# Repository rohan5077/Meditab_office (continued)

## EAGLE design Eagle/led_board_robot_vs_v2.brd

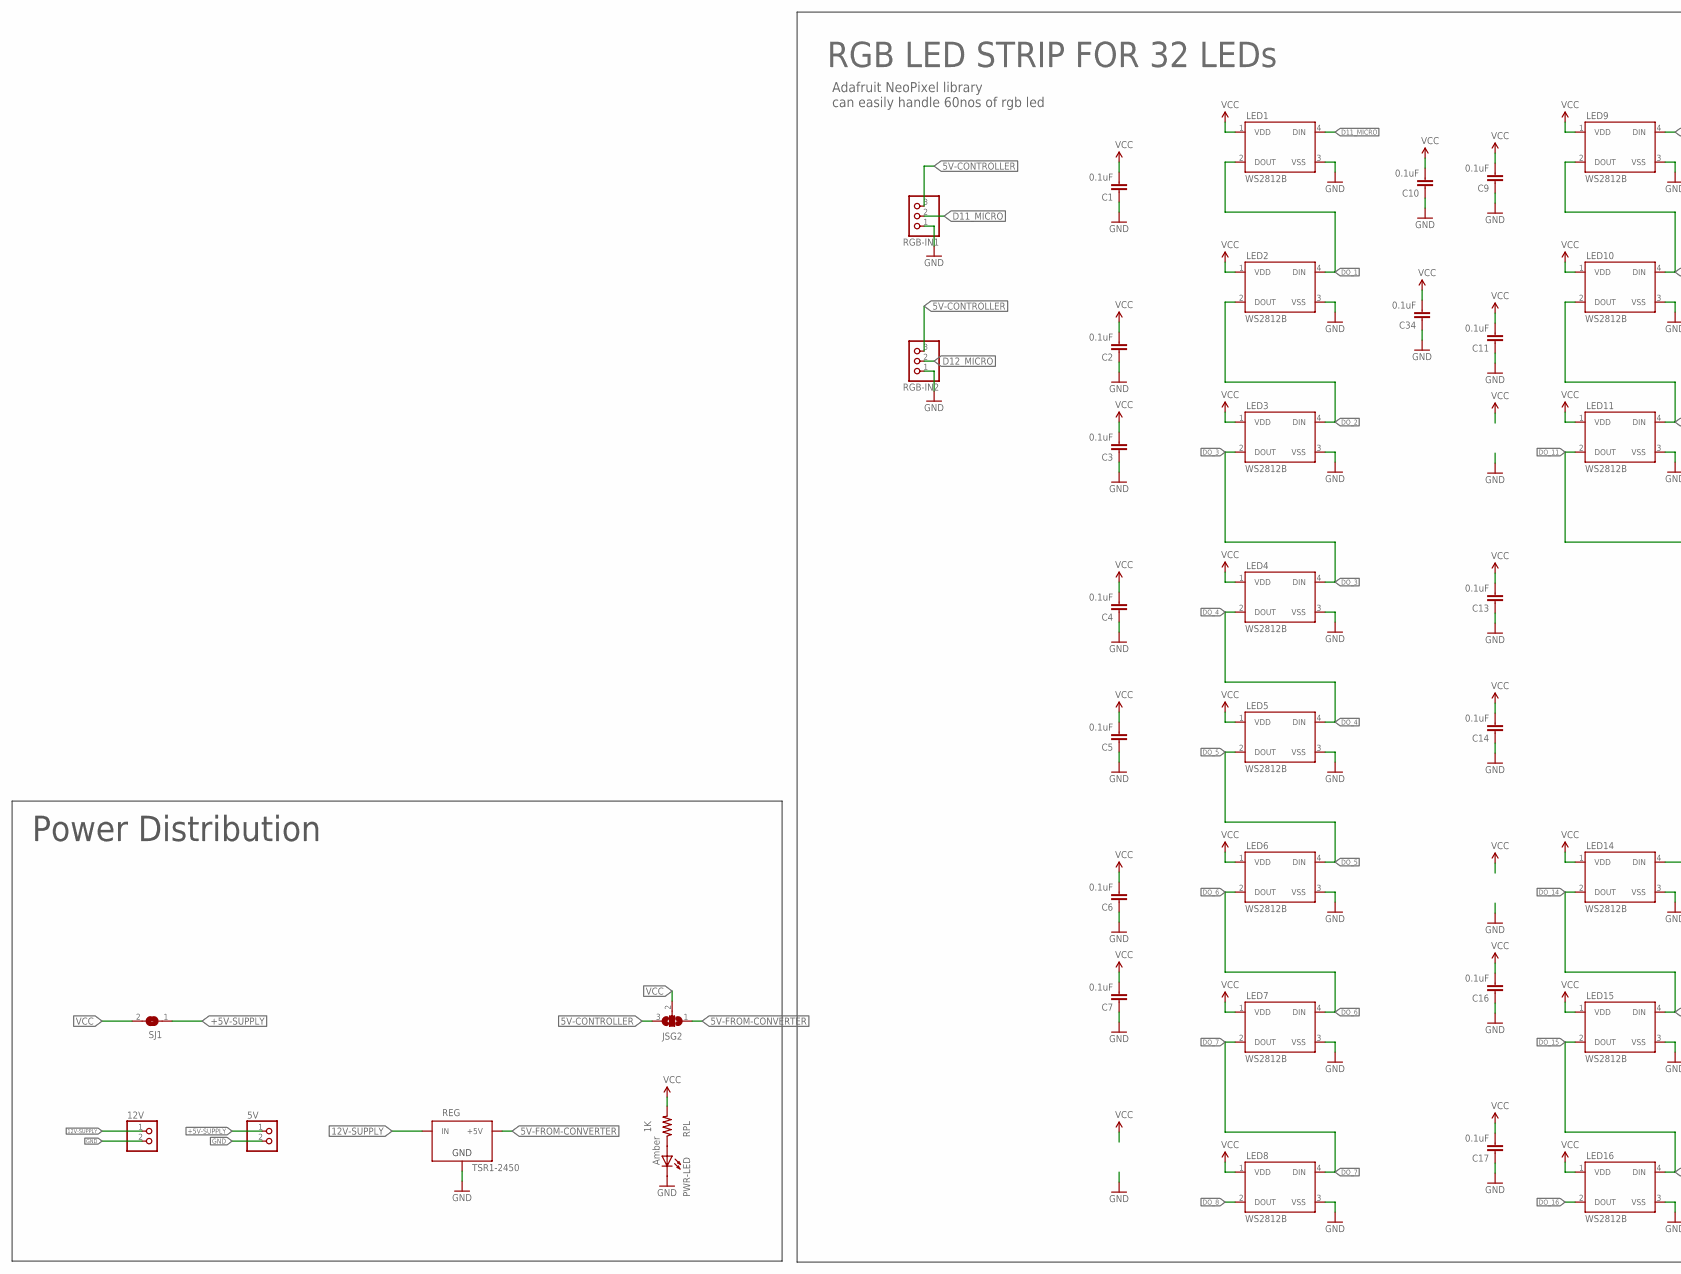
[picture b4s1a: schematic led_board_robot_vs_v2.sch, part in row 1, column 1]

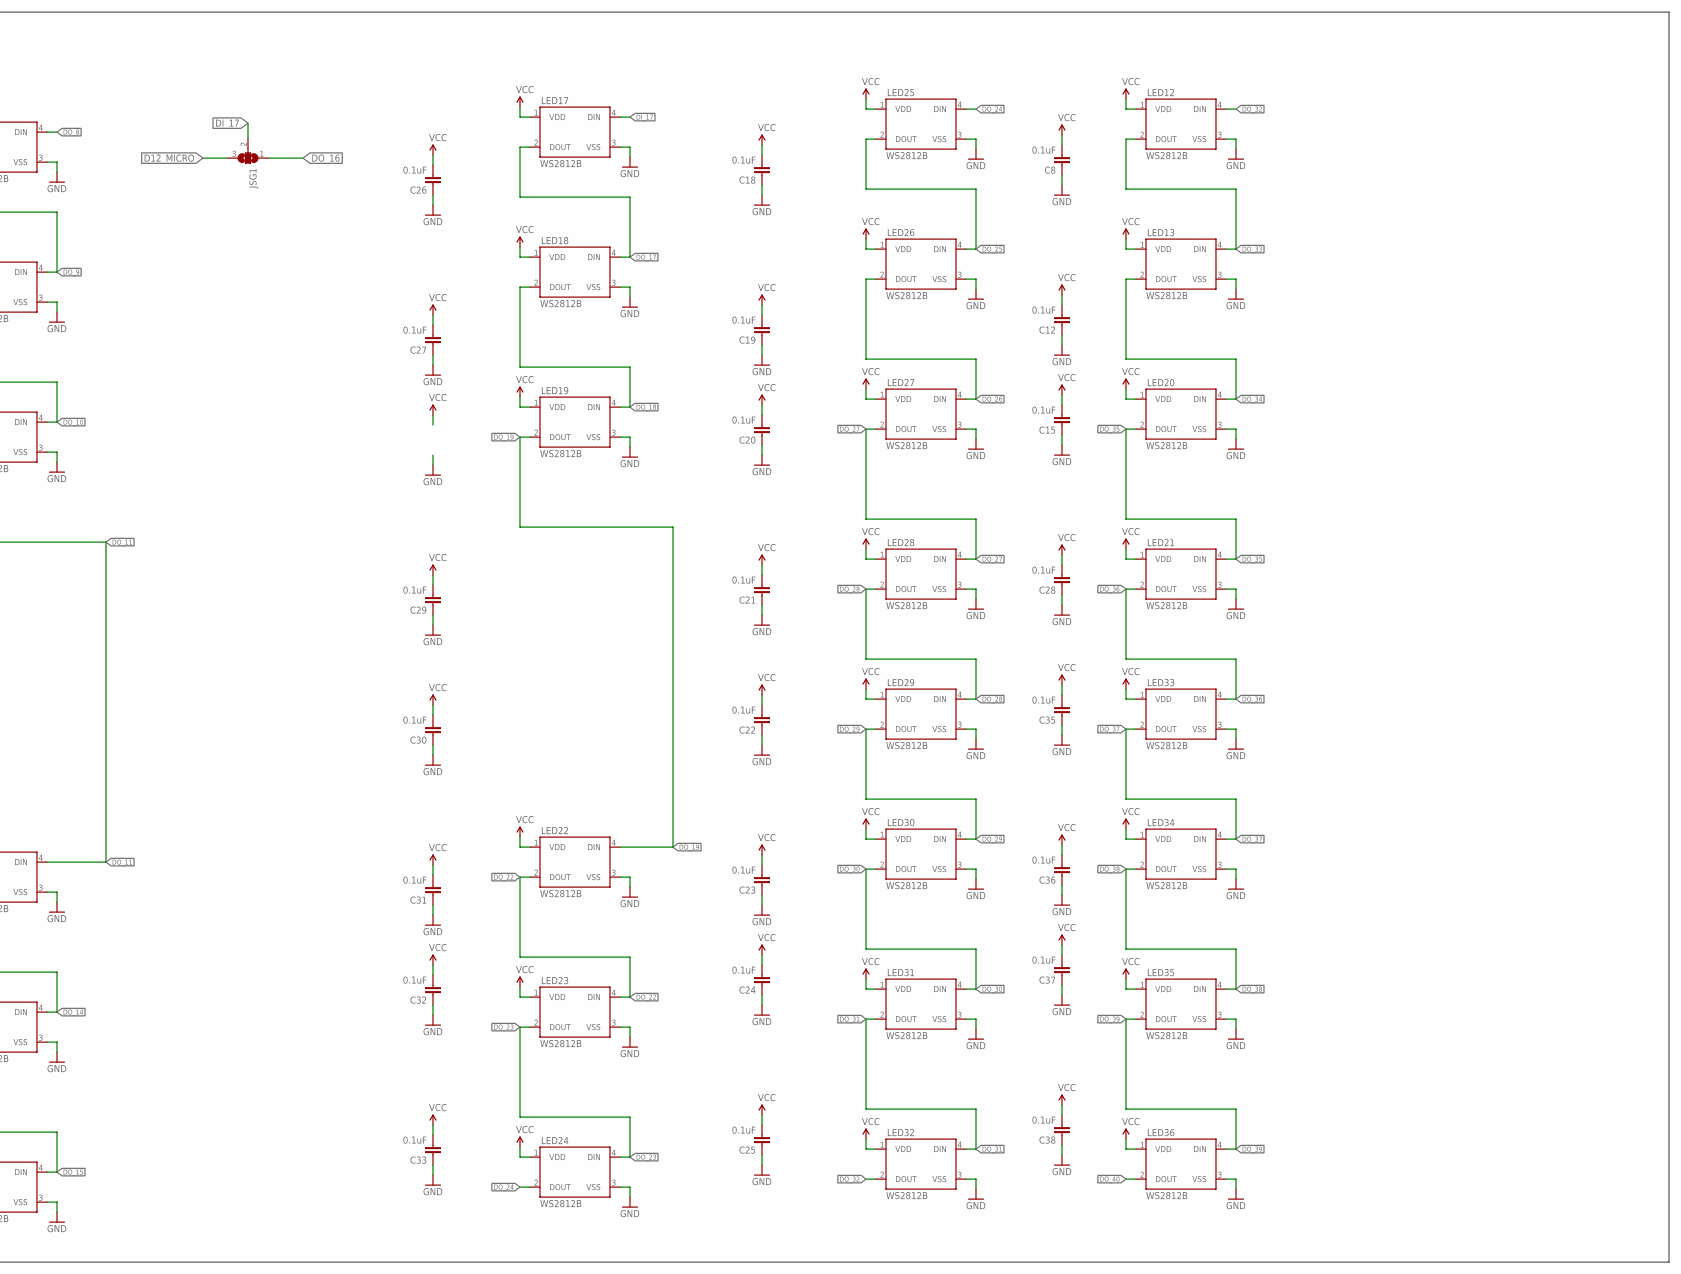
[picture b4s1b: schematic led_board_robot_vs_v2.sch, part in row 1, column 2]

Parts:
5V, 12V: PINHD-1X2; 1X02
C1, C2, C3, C4, C5, C6, C7, C8, C9, C10, C11, C12, C13, C14, C15, C16, C17, C18, C19, C20, C21, C22, C23, C24, C25, C26, C27, C28, C29, C30, C31, C32, C33, C34, C35, C36, C37, C38: 0.1uF; 0603-CAP
JSG1, JSG2: SJ2WW; SJ_2W
LED1, LED2, LED3, LED4, LED5, LED6, LED7, LED8, LED9, LED10, LED11, LED12, LED13, LED14, LED15, LED16, LED17, LED18, LED19, LED20, LED21, LED22, LED23, LED24, LED25, LED26, LED27, LED28, LED29, LED30, LED31, LED32, LED33, LED34, LED35, LED36: WS2812B
PWR-LED: Amber; LED-0603
REG: TSR1-2450; TSR-1
RGB-IN1, RGB-IN2: PINHD-1X3; 1X03
RPL: 1K; 0603-RES
SJ1: SJW

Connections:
5V-CONTROLLER: JSG2.3, RGB-IN1.3, RGB-IN2.3
5V-FROM-CONVERTER: JSG2.1, REG.3 (+5V)
12V-SUPPLY: 12V.1, REG.1 (IN)
+5V-SUPPLY: 5V.1, SJ1.1
D11_MICRO: LED1.4 (DIN), RGB-IN1.2
D12_MICRO: JSG1.3, RGB-IN2.2
DI_17: JSG1.2, LED17.4 (DIN)
DO_1: LED1.2 (DOUT), LED2.4 (DIN)
DO_2: LED2.2 (DOUT), LED3.4 (DIN)
DO_3: LED3.2 (DOUT), LED4.4 (DIN)
DO_4: LED4.2 (DOUT), LED5.4 (DIN)
DO_5: LED5.2 (DOUT), LED6.4 (DIN)
DO_6: LED6.2 (DOUT), LED7.4 (DIN)
DO_7: LED7.2 (DOUT), LED8.4 (DIN)
DO_8: LED8.2 (DOUT), LED9.4 (DIN)
DO_9: LED9.2 (DOUT), LED10.4 (DIN)
DO_10: LED10.2 (DOUT), LED11.4 (DIN)
DO_11: LED11.2 (DOUT), LED14.4 (DIN)
DO_14: LED14.2 (DOUT), LED15.4 (DIN)
DO_15: LED15.2 (DOUT), LED16.4 (DIN)
DO_16: JSG1.1, LED16.2 (DOUT)
DO_17: LED17.2 (DOUT), LED18.4 (DIN)
DO_18: LED18.2 (DOUT), LED19.4 (DIN)
DO_19: LED19.2 (DOUT), LED22.4 (DIN)
DO_22: LED22.2 (DOUT), LED23.4 (DIN)
DO_23: LED23.2 (DOUT), LED24.4 (DIN)
DO_24: LED24.2 (DOUT), LED25.4 (DIN)
DO_25: LED25.2 (DOUT), LED26.4 (DIN)
DO_26: LED26.2 (DOUT), LED27.4 (DIN)
DO_27: LED27.2 (DOUT), LED28.4 (DIN)
DO_28: LED28.2 (DOUT), LED29.4 (DIN)
DO_29: LED29.2 (DOUT), LED30.4 (DIN)
DO_30: LED30.2 (DOUT), LED31.4 (DIN)
DO_31: LED31.2 (DOUT), LED32.4 (DIN)
DO_32: LED12.4 (DIN), LED32.2 (DOUT)
DO_33: LED12.2 (DOUT), LED13.4 (DIN)
DO_34: LED13.2 (DOUT), LED20.4 (DIN)
DO_35: LED20.2 (DOUT), LED21.4 (DIN)
DO_36: LED21.2 (DOUT), LED33.4 (DIN)
DO_37: LED33.2 (DOUT), LED34.4 (DIN)
DO_38: LED34.2 (DOUT), LED35.4 (DIN)
DO_39: LED35.2 (DOUT), LED36.4 (DIN)
DO_40: LED36.2 (DOUT)
GND: 5V.2, 12V.2, C1.1, C2.1, C3.1, C4.1, C5.1, C6.1, C7.1, C8.1, C9.1, C10.1, C11.1, C12.1, C13.1, C14.1, C15.1, C16.1, C17.1, C18.1, C19.1, C20.1, C21.1, C22.1, C23.1, C24.1, C25.1, C26.1, C27.1, C28.1, C29.1, C30.1, C31.1, C32.1, C33.1, C34.1, C35.1, C36.1, C37.1, C38.1, LED1.3 (VSS), LED2.3 (VSS), LED3.3 (VSS), LED4.3 (VSS), LED5.3 (VSS), LED6.3 (VSS), LED7.3 (VSS), LED8.3 (VSS), LED9.3 (VSS), LED10.3 (VSS), LED11.3 (VSS), LED12.3 (VSS), LED13.3 (VSS), LED14.3 (VSS), LED15.3 (VSS), LED16.3 (VSS), LED17.3 (VSS), LED18.3 (VSS), LED19.3 (VSS), LED20.3 (VSS), LED21.3 (VSS), LED22.3 (VSS), LED23.3 (VSS), LED24.3 (VSS), LED25.3 (VSS), LED26.3 (VSS), LED27.3 (VSS), LED28.3 (VSS), LED29.3 (VSS), LED30.3 (VSS), LED31.3 (VSS), LED32.3 (VSS), LED33.3 (VSS), LED34.3 (VSS), LED35.3 (VSS), LED36.3 (VSS), PWR-LED.C, REG.2 (GND), RGB-IN1.1, RGB-IN2.1
unnamed: PWR-LED.A, RPL.1
VCC: C1.2, C2.2, C3.2, C4.2, C5.2, C6.2, C7.2, C8.2, C9.2, C10.2, C11.2, C12.2, C13.2, C14.2, C15.2, C16.2, C17.2, C18.2, C19.2, C20.2, C21.2, C22.2, C23.2, C24.2, C25.2, C26.2, C27.2, C28.2, C29.2, C30.2, C31.2, C32.2, C33.2, C34.2, C35.2, C36.2, C37.2, C38.2, JSG2.2, LED1.1 (VDD), LED2.1 (VDD), LED3.1 (VDD), LED4.1 (VDD), LED5.1 (VDD), LED6.1 (VDD), LED7.1 (VDD), LED8.1 (VDD), LED9.1 (VDD), LED10.1 (VDD), LED11.1 (VDD), LED12.1 (VDD), LED13.1 (VDD), LED14.1 (VDD), LED15.1 (VDD), LED16.1 (VDD), LED17.1 (VDD), LED18.1 (VDD), LED19.1 (VDD), LED20.1 (VDD), LED21.1 (VDD), LED22.1 (VDD), LED23.1 (VDD), LED24.1 (VDD), LED25.1 (VDD), LED26.1 (VDD), LED27.1 (VDD), LED28.1 (VDD), LED29.1 (VDD), LED30.1 (VDD), LED31.1 (VDD), LED32.1 (VDD), LED33.1 (VDD), LED34.1 (VDD), LED35.1 (VDD), LED36.1 (VDD), RPL.2, SJ1.2

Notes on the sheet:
Adafruit NeoPixel library can easily handle 60nos of rgb led
RGB LED STRIP FOR 32 LEDs
Power Distribution

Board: 2 copper layers, 84 parts (2 on the bottom side), 45 nets, no tracks yet.

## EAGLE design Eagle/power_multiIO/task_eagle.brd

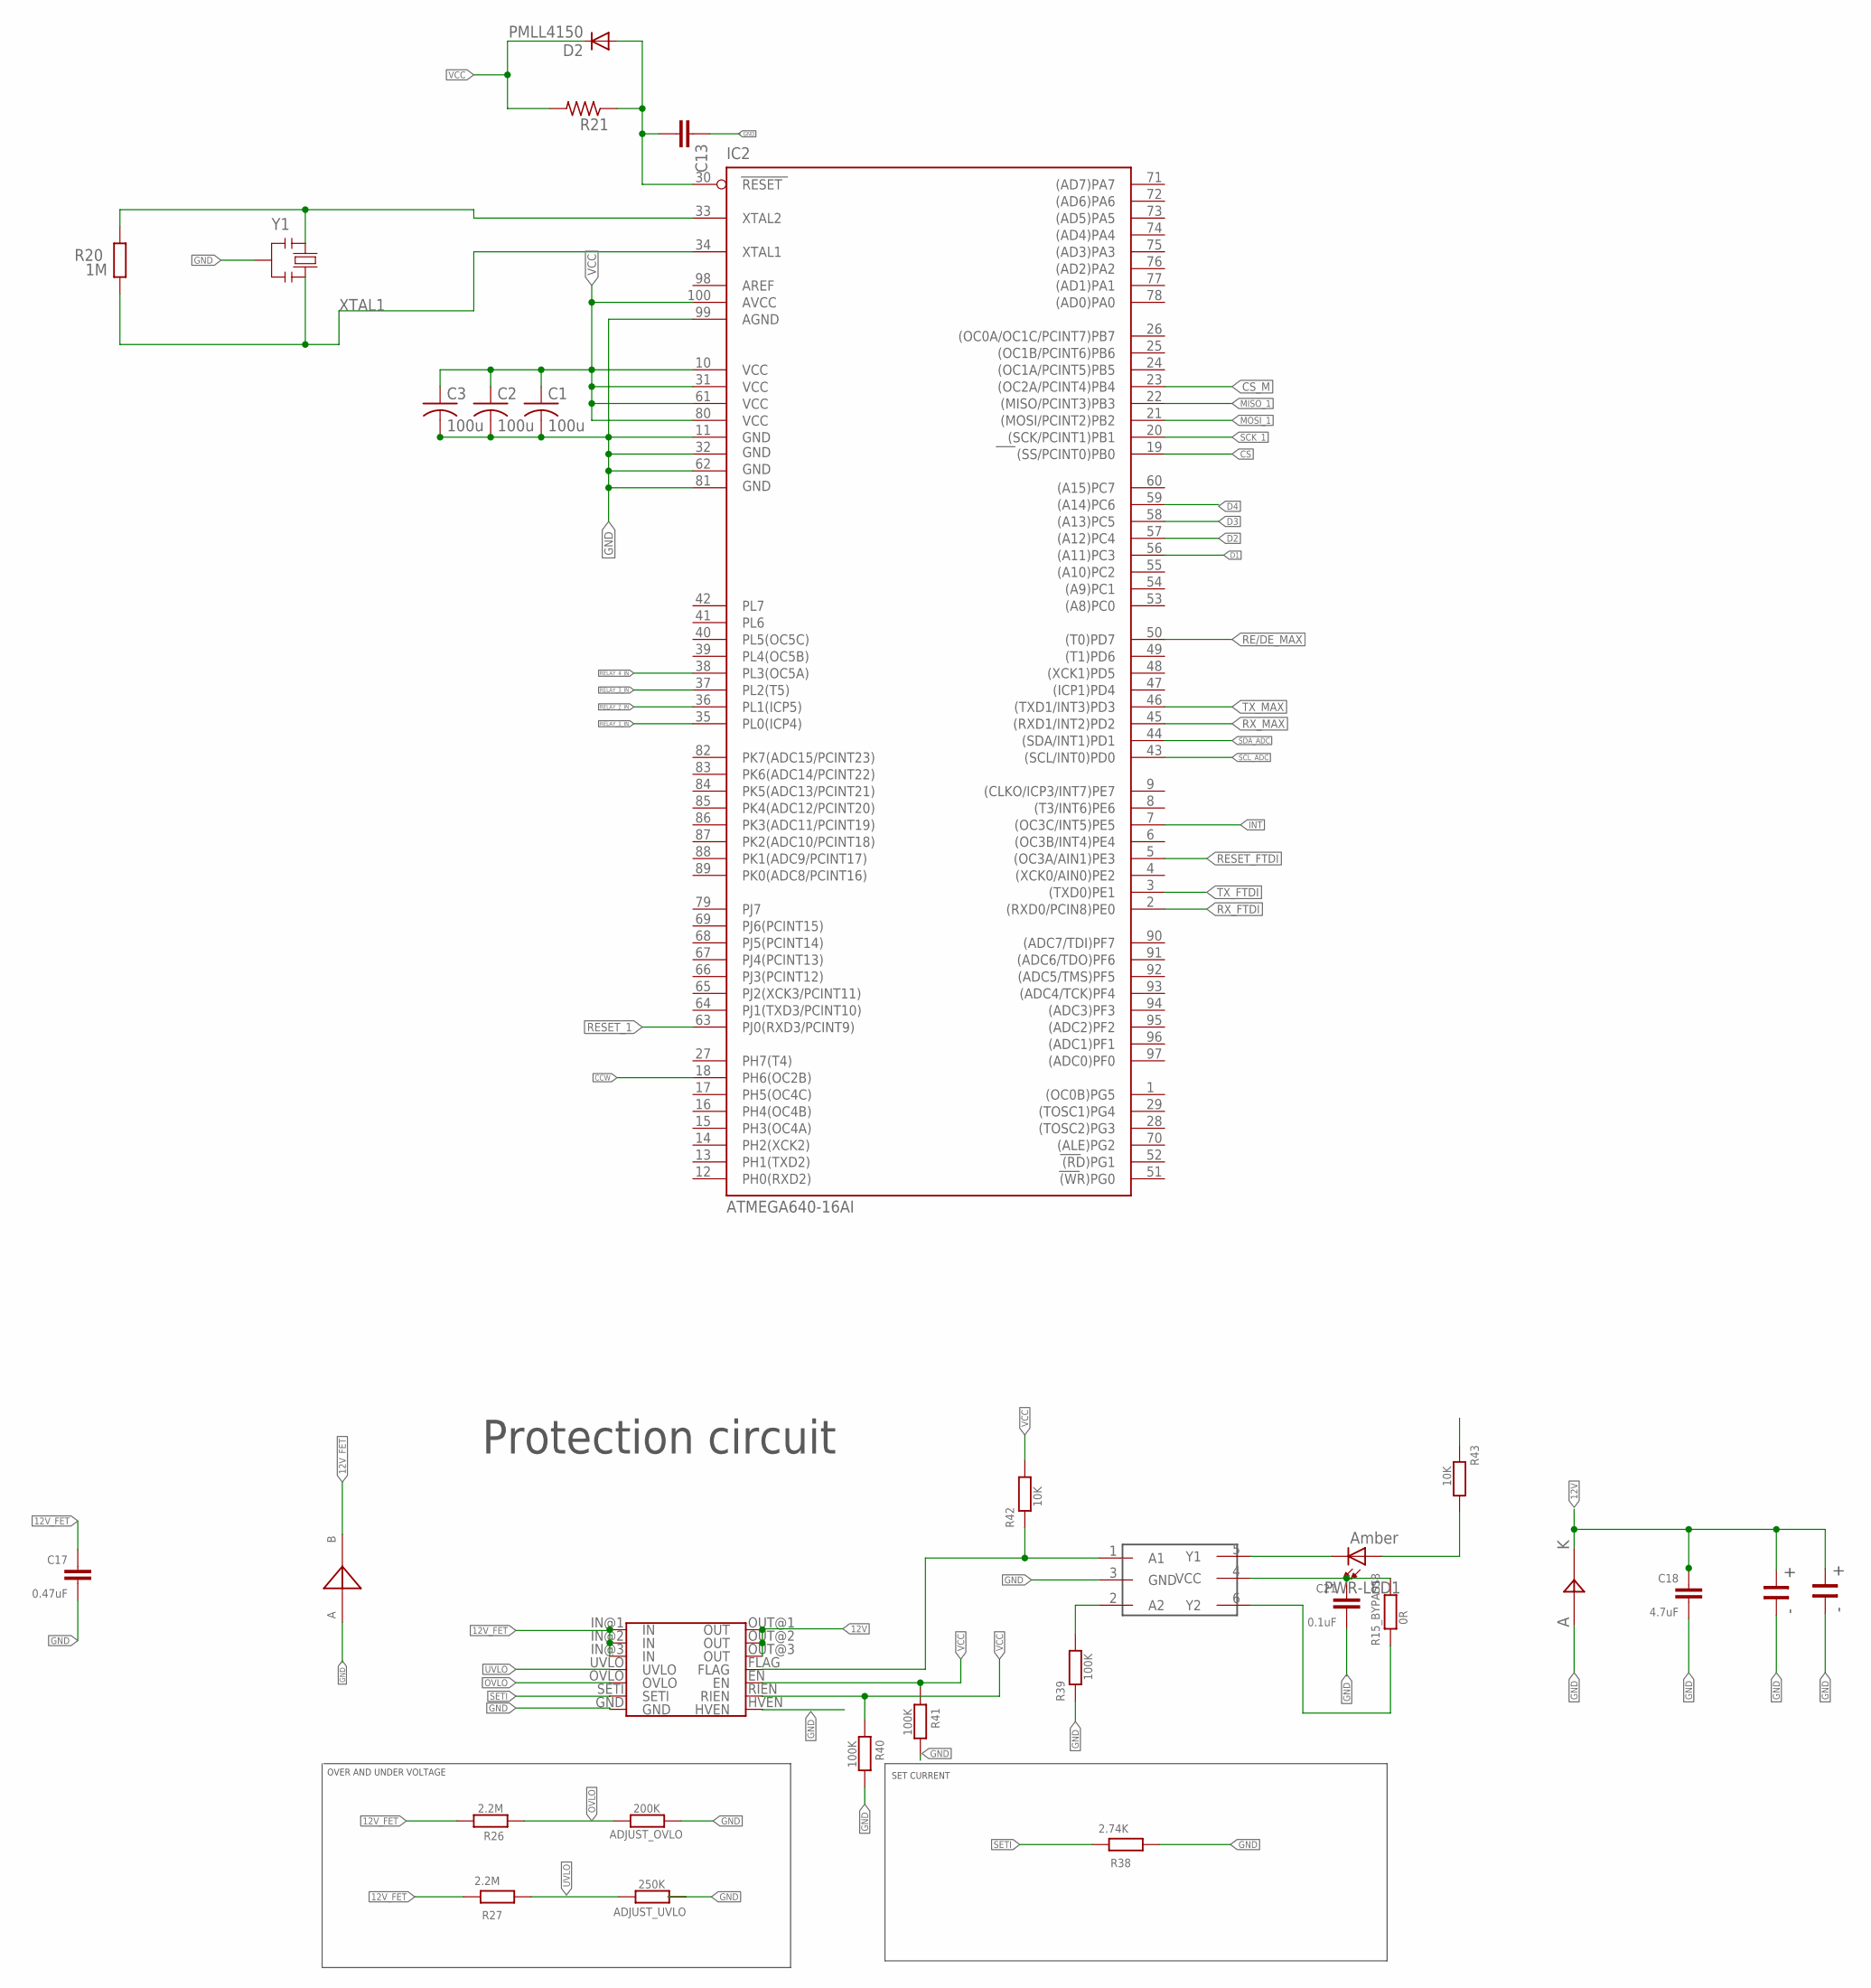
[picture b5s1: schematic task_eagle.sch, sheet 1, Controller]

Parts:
ADJUST_OVLO: 200K; R0603-ROUND
ADJUST_UVLO: 250K; R0603-ROUND
C1, C2, C3: 100u; C0603
C13: CC0603; C0603
C17: 0.47uF; C0603-ROUND
C18: 4.7uF; C0603-ROUND
C21: 0.1uF; C0603-ROUND
D2: PMLL4150; SOD80C
IC2: ATMEGA640-16AI; TQFP100
PWR-LED1: Amber; LED-0603
R15_BYPASS8: 0R; R0603-ROUND
R20: 1M; R0603-ROUND
R21: R-US_R0603; R0603
R26, R27: 2.2M; R0603-ROUND
R38: 2.74K; R0603-ROUND
R39, R40, R41: 100K; R0603-ROUND
R42, R43: 10K; R0603-ROUND
U$37: MAX14571; TSSOP14
U$38: STPS5L60S; SMC
U$39: SM6T36CA; DO214AA
U$40: NC7WZ07P6X; SC70-6L
U$41, U$42: EEV-FK1H331Q; EEVFK1H331Q
Y1: RESONATORMU; RESONATOR

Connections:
12V: C18.1, U$37.OUT@1 (OUT), U$37.OUT@2 (OUT), U$37.OUT@3 (OUT), U$38.1, U$41.P$2, U$42.P$2; also elsewhere on the board
12V_FET: C17.1, R26.1, R27.1, U$37.IN@1 (IN), U$37.IN@2 (IN), U$37.IN@3 (IN), U$39.C; also elsewhere on the board
CCW: IC2.18 (PH6(OC2B)); also elsewhere on the board
CS: IC2.19 ((SS/PCINT0)PB0); also elsewhere on the board
CS_M: IC2.23 ((OC2A/PCINT4)PB4); also elsewhere on the board
D1: IC2.56 ((A11)PC3); also elsewhere on the board
D2: IC2.57 ((A12)PC4); also elsewhere on the board
D3: IC2.58 ((A13)PC5); also elsewhere on the board
D4: IC2.59 ((A14)PC6); also elsewhere on the board
GND: ADJUST_OVLO.2, ADJUST_UVLO.2, C1.2, C2.2, C3.2, C13.1, C17.2, C18.2, C21.2, IC2.11 (GND), IC2.32 (GND1), IC2.62 (GND2), IC2.81 (GND3), IC2.99 (AGND), R38.2, R39.2, R40.1, R41.1, U$37.GND, U$37.HVEN, U$38.2, U$39.A, U$40.3 (GND), U$41.P$1, U$42.P$1, Y1.2; also elsewhere on the board
INT: IC2.7 ((OC3C/INT5)PE5); also elsewhere on the board
MISO_1: IC2.22 ((MISO/PCINT3)PB3); also elsewhere on the board
MOSI_1: IC2.21 ((MOSI/PCINT2)PB2); also elsewhere on the board
unnamed: C13.2, D2.A, IC2.30 (RESET), R21.1
unnamed: PWR-LED1.A, R43.1
unnamed: PWR-LED1.C, U$40.5 (Y1)
unnamed: R39.1, U$40.2 (A2)
unnamed: R15_BYPASS8.2, U$40.6 (Y2)
OVLO: ADJUST_OVLO.1, R26.2, U$37.OVLO
RE/DE_MAX: IC2.50 ((T0)PD7); also elsewhere on the board
RELAY_1_IN: IC2.35 (PL0(ICP4)); also elsewhere on the board
RELAY_2_IN: IC2.36 (PL1(ICP5)); also elsewhere on the board
RELAY_3_IN: IC2.37 (PL2(T5)); also elsewhere on the board
RELAY_4_IN: IC2.38 (PL3(OC5A)); also elsewhere on the board
RESET_1: IC2.63 (PJ0(RXD3/PCINT9)); also elsewhere on the board
RESET_FTDI: IC2.5 ((OC3A/AIN1)PE3); also elsewhere on the board
RX_FTDI: IC2.2 ((RXD0/PCIN8)PE0); also elsewhere on the board
RX_MAX: IC2.45 ((RXD1/INT2)PD2); also elsewhere on the board
SCK_1: IC2.20 ((SCK/PCINT1)PB1); also elsewhere on the board
SCL_ADC: IC2.43 ((SCL/INT0)PD0); also elsewhere on the board
SDA_ADC: IC2.44 ((SDA/INT1)PD1); also elsewhere on the board
SETI: R38.1, U$37.SETI
TX_FTDI: IC2.3 ((TXD0)PE1); also elsewhere on the board
TX_MAX: IC2.46 ((TXD1/INT3)PD3); also elsewhere on the board
UVLO: ADJUST_UVLO.1, R27.2, U$37.UVLO
VCC: C1.1, C2.1, C3.1, C21.1, D2.C, IC2.10 (VCC), IC2.31 (VCC1), IC2.61 (VCC2), IC2.80 (VCC3), IC2.100 (AVCC), R15_BYPASS8.1, R21.2, R40.2, R41.2, R42.1, R43.2, U$37.EN, U$37.RIEN, U$40.4 (VCC); also elsewhere on the board
XTAL1: IC2.34 (XTAL1), R20.1, Y1.3
XTAL2: IC2.33 (XTAL2), R20.2, Y1.1
XX: R42.2, U$37.FLAG, U$40.1 (A1)

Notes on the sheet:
Protection circuit
OVER AND UNDER VOLTAGE
SET CURRENT

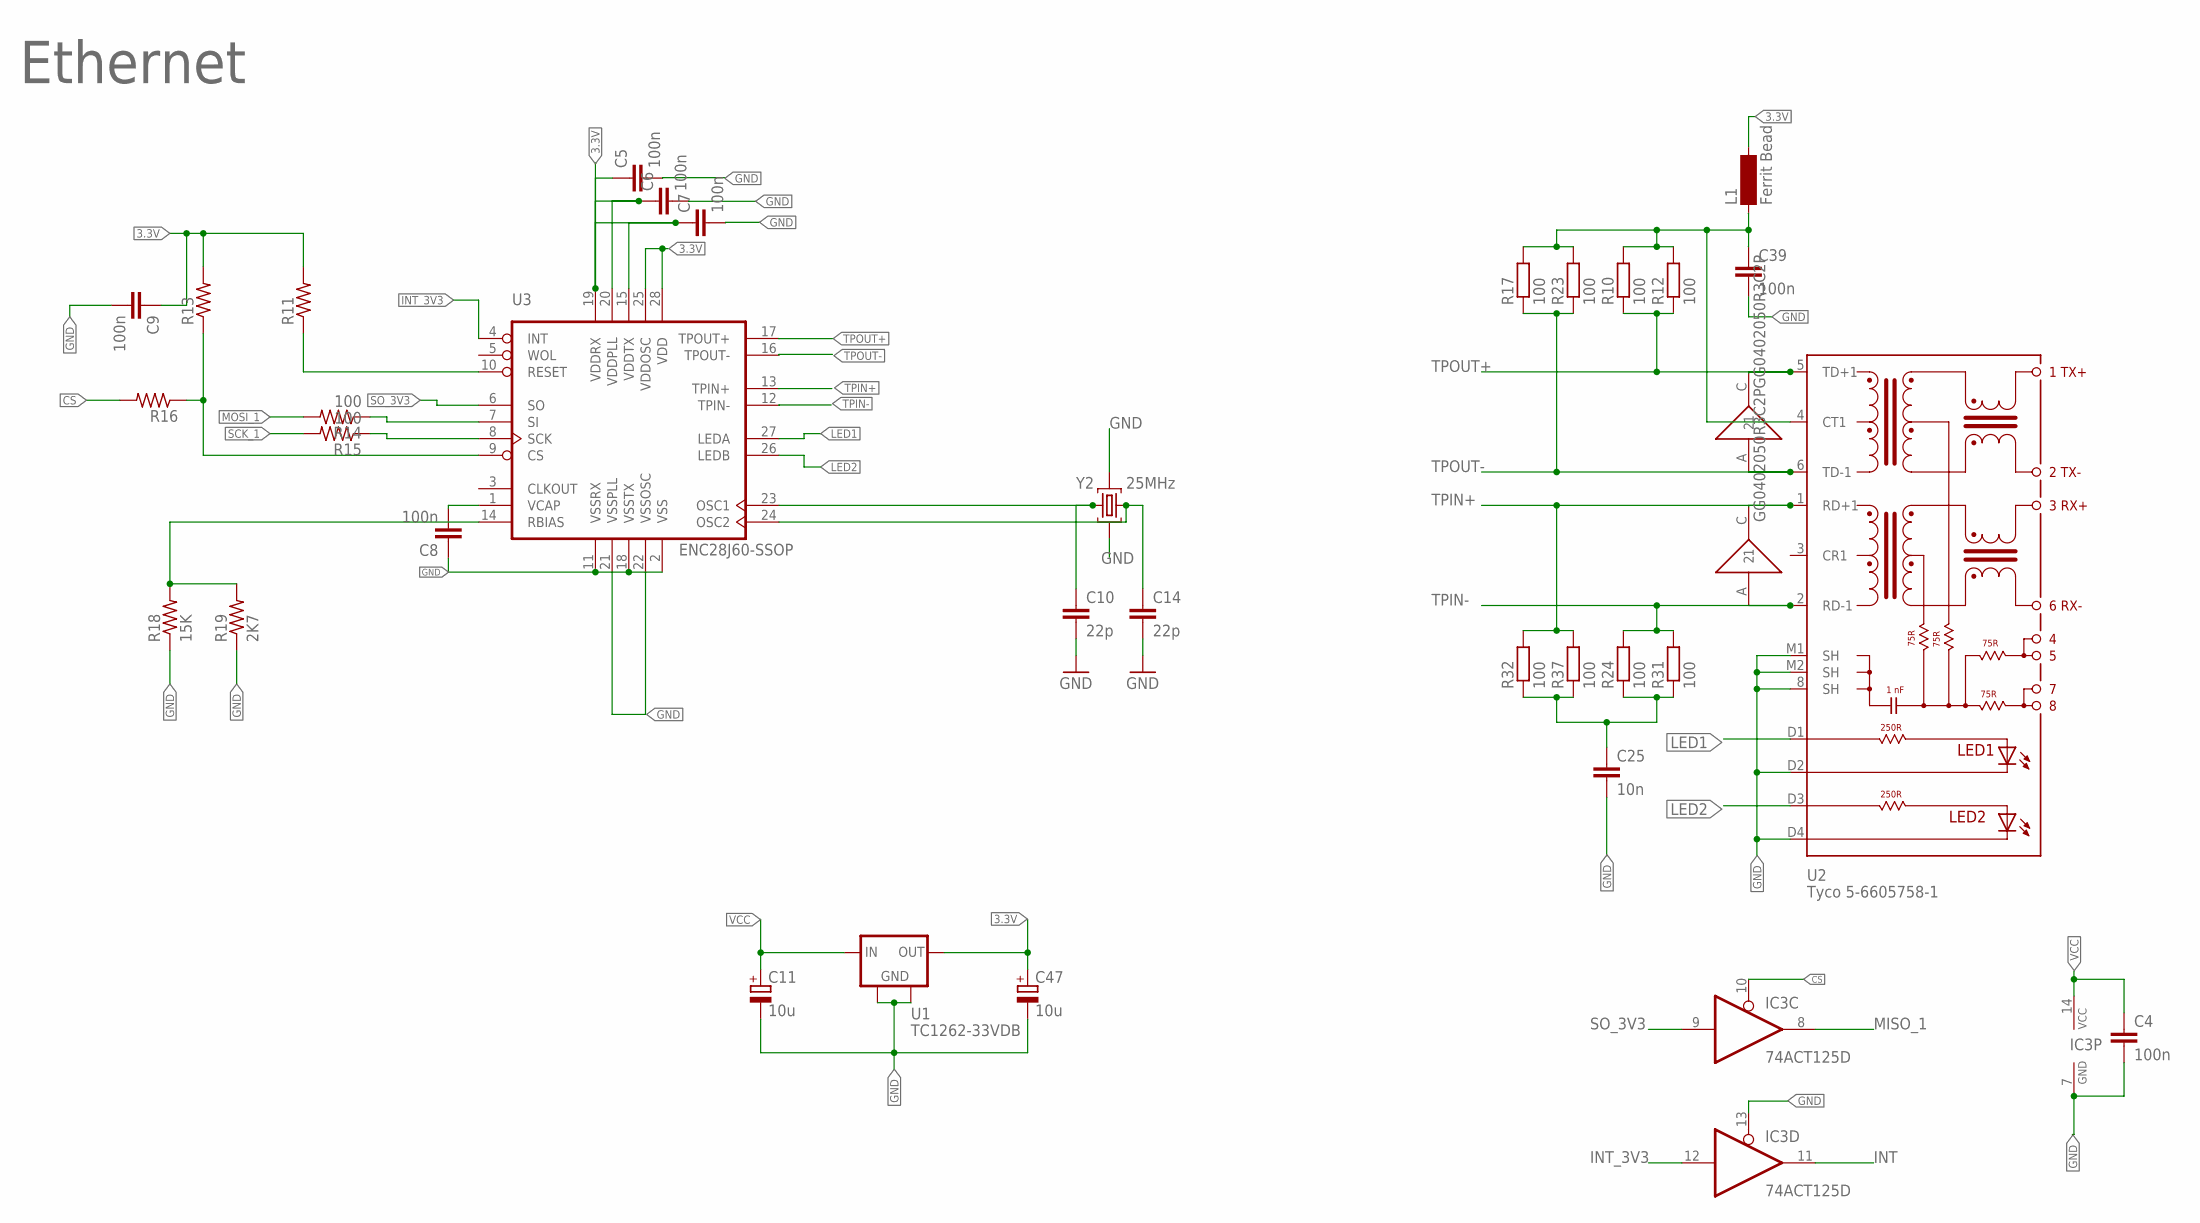
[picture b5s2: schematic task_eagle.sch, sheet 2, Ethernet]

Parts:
C4, C5, C6, C7, C8, C9, C39: 100n; C0603
C10, C14: 22p; C0603
C11, C47: 10u; 153CLV-0605
C25: 10n; C0603
IC3: 74ACT125D; SO14
L1: Ferrit Bead; SM-1206
R10, R12, R14, R15, R17, R23, R24, R31, R32, R37: 100; R0603
R11, R13, R16: R-US_R0603; R0603
R18: 15K; R0603
R19: 2K7; R0603
U1: TC1262-33VDB; SOT223
U2: Tyco 5-6605758-1; 5-6605758-1
U3: ENC28J60-SSOP; SSOP28
U$6, U$7: GG0402050R3C2P; 0402
Y2: 25MHz; CRYSTAL-3.2-2.5

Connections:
3.3V: C5.1, C6.1, C7.1, C9.1, C47.+, L1.2, R11.2, R13.2, U1.3 (OUT), U3.15 (VDDTX), U3.19 (VDDRX), U3.20 (VDDPLL), U3.25 (VDDOSC), U3.28 (VDD); also elsewhere on the board
CS: IC3.10 (OE), R16.2; also elsewhere on the board
GND: C4.2, C5.2, C6.2, C7.2, C8.1, C9.2, C10.2, C11.-, C14.2, C25.2, C39.2, C47.-, IC3.7 (GND), IC3.13 (OE), R18.1, R19.1, U1.2 (GND), U1.4 (GND), U2.8 (SH), U2.D2, U2.D4, U2.M1 (SH), U2.M2 (SH), U3.2 (VSS), U3.11 (VSSRX), U3.18 (VSSTX), U3.21 (VSSPLL), U3.22 (VSSOSC), Y2.2 (GND), Y2.4 (GND); also elsewhere on the board
INT: IC3.11 (O); also elsewhere on the board
INT_3V3: IC3.12 (I), U3.4 (INT)
LED1: U2.D1, U3.27 (LEDA)
LED2: U2.D3, U3.26 (LEDB)
MISO_1: IC3.8 (O); also elsewhere on the board
MOSI_1: R14.2; also elsewhere on the board
unnamed: R11.1, U3.10 (RESET)
unnamed: R13.1, R16.1, U3.9 (CS)
unnamed: R14.1, U3.7 (SI)
unnamed: R18.2, R19.2, U3.14 (RBIAS)
unnamed: R15.1, U3.8 (SCK)
unnamed: C8.2, U3.1 (VCAP)
unnamed: C10.1, U3.23 (OSC1), Y2.3 (C2)
unnamed: C25.1, R24.1, R31.1, R32.1, R37.1
unnamed: C39.1, L1.1, R10.2, R12.2, R17.2, R23.2, U2.4 (CT1)
unnamed: C14.1, U3.24 (OSC2), Y2.1 (C1)
SCK_1: R15.2; also elsewhere on the board
SO_3V3: IC3.9 (I), U3.6 (SO)
TPIN+: R32.2, R37.2, U2.1 (RD+1), U3.13 (TPIN+), U$7.C (2)
TPIN-: R24.2, R31.2, U2.2 (RD-1), U3.12 (TPIN-), U$7.A (1)
TPOUT+: R10.1, R12.1, U2.5 (TD+1), U3.17 (TPOUT+), U$6.C (2)
TPOUT-: R17.1, R23.1, U2.6 (TD-1), U3.16 (TPOUT-), U$6.A (1)
VCC: C4.1, C11.+, IC3.14 (VCC), U1.1 (IN); also elsewhere on the board

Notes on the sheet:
Ethernet

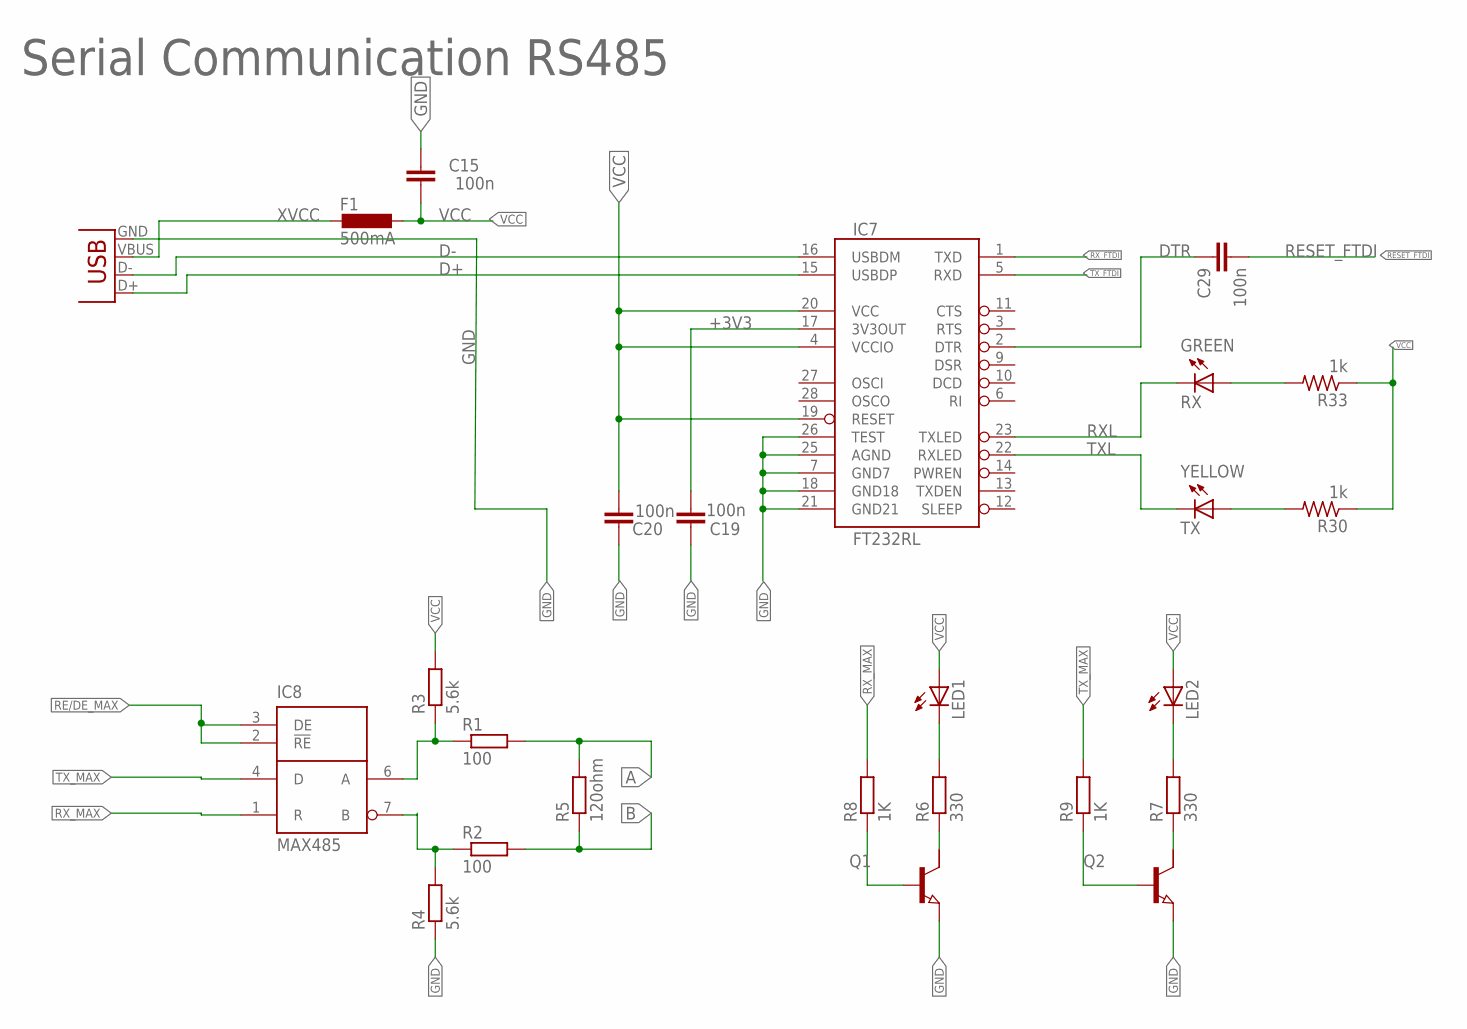
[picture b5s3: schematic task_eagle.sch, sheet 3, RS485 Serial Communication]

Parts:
C15: 100n; C0603
C19, C20, C29: 100n; C0603-ROUND
F1: 500mA; L1812
IC7: FT232RL; SSOP28DB
IC8: MAX485; SO-08
LED1, LED2: LED_ESML0603; LED_SML0603
Q1, Q2: NPN-TRANSISTIOR-2COLSOT89; SOT89
R1, R2: 100; R0603
R3, R4: 5.6k; R0603
R5: 120ohm; R0603
R6, R7: 330; R0603
R8, R9: 1K; R0603
R30, R33: 1k; R0603
RX: GREEN; CHIPLED_0603
TX: YELLOW; CHIPLED_0603
USB: USB; USB-B-PTH-VERTICAL

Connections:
+3V3: C19.2, IC7.17 (3V3OUT)
A: R1.2, R5.2; also elsewhere on the board
B: R2.2, R5.1; also elsewhere on the board
D+: IC7.15 (USBDP), USB.D+
D-: IC7.16 (USBDM), USB.D-
DTR: C29.1, IC7.2 (DTR)
GND: C15.2, C19.1, C20.2, IC7.7 (GND7), IC7.18 (GND18), IC7.21 (GND21), IC7.25 (AGND), IC7.26 (TEST), IC8.5 (GND), Q1.3 (E), Q2.3 (E), R4.1, USB.GND; also elsewhere on the board
unnamed: IC8.6 (A), R1.1, R3.1
unnamed: IC8.7 (B), R2.1, R4.2
unnamed: R30.2, TX.A
unnamed: LED1.C, R6.2
unnamed: LED2.C, R7.2
unnamed: Q1.2 (C), R6.1
unnamed: Q2.2 (C), R7.1
unnamed: Q2.1 (B), R9.1
unnamed: Q1.1 (B), R8.1
unnamed: R33.2, RX.A
RE/DE_MAX: IC8.2 (!RE), IC8.3 (DE); also elsewhere on the board
RESET_FTDI: C29.2; also elsewhere on the board
RXL: IC7.23 (TXLED), RX.C
RX_FTDI: IC7.1 (TXD); also elsewhere on the board
RX_MAX: IC8.1 (R), R8.2; also elsewhere on the board
TXL: IC7.22 (RXLED), TX.C
TX_FTDI: IC7.5 (RXD); also elsewhere on the board
TX_MAX: IC8.4 (D), R9.2; also elsewhere on the board
VCC: C15.1, C20.1, F1.1, IC7.4 (VCCIO), IC7.19 (RESET), IC7.20 (VCC), IC8.8 (VCC), LED1.A, LED2.A, R3.2, R30.1, R33.1; also elsewhere on the board
XVCC: F1.2, USB.VBUS

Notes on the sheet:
Serial Communication RS485
